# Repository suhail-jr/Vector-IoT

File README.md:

# Vector-IoT
Vector IoT : World’s smallest and powerful fully opensource  fully-featured ESP32 development board designed to unlock the power of the ESP32’s dual-core 240MHz and internet connectivity, in a package smaller than your thumb!

 ~ Current Status: Prototype boards sponsored by [jlcpcb.com](https://jlcpcb.com) ~
     
     Note: This design was performed in Eagle 9.2.0 , you will need a atleast eagle 9.2.0 or higher version to open and edit these source files. 
           # Chance for bugs : High

# Rendered Footage of the PCB

## Licence
 * Hardware in this repository is licenced under Creative Commons BY-SA

 ## OSHW Certification
 TBD (Will apply when prototypes tested)

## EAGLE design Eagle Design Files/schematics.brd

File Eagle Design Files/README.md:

# Vector-IoT
Vector IoT : World’s smallest and powerful fully opensource  fully-featured ESP32 development board designed to unlock the power of the ESP32’s dual-core 240MHz and internet connectivity, in a package smaller than your thumb! Order your pcb from [jlcpcb.com](https://jlcpcb.com)

 ~ Current Status: Prototype boards sponsored by [jlcpcb.com](https://jlcpcb.com) ~
     
     Note: This design was performed in Eagle 9.2.0 , you will need a atleast eagle 9.2.0 or higher version to open and edit these source files. 
           # Chance for bugs : High

# Rendered Footage of the PCB

## Licence
 * Hardware in this repository is licenced under Creative Commons BY-SA

 ## OSHW Certification
 TBD (Will apply when prototypes tested)

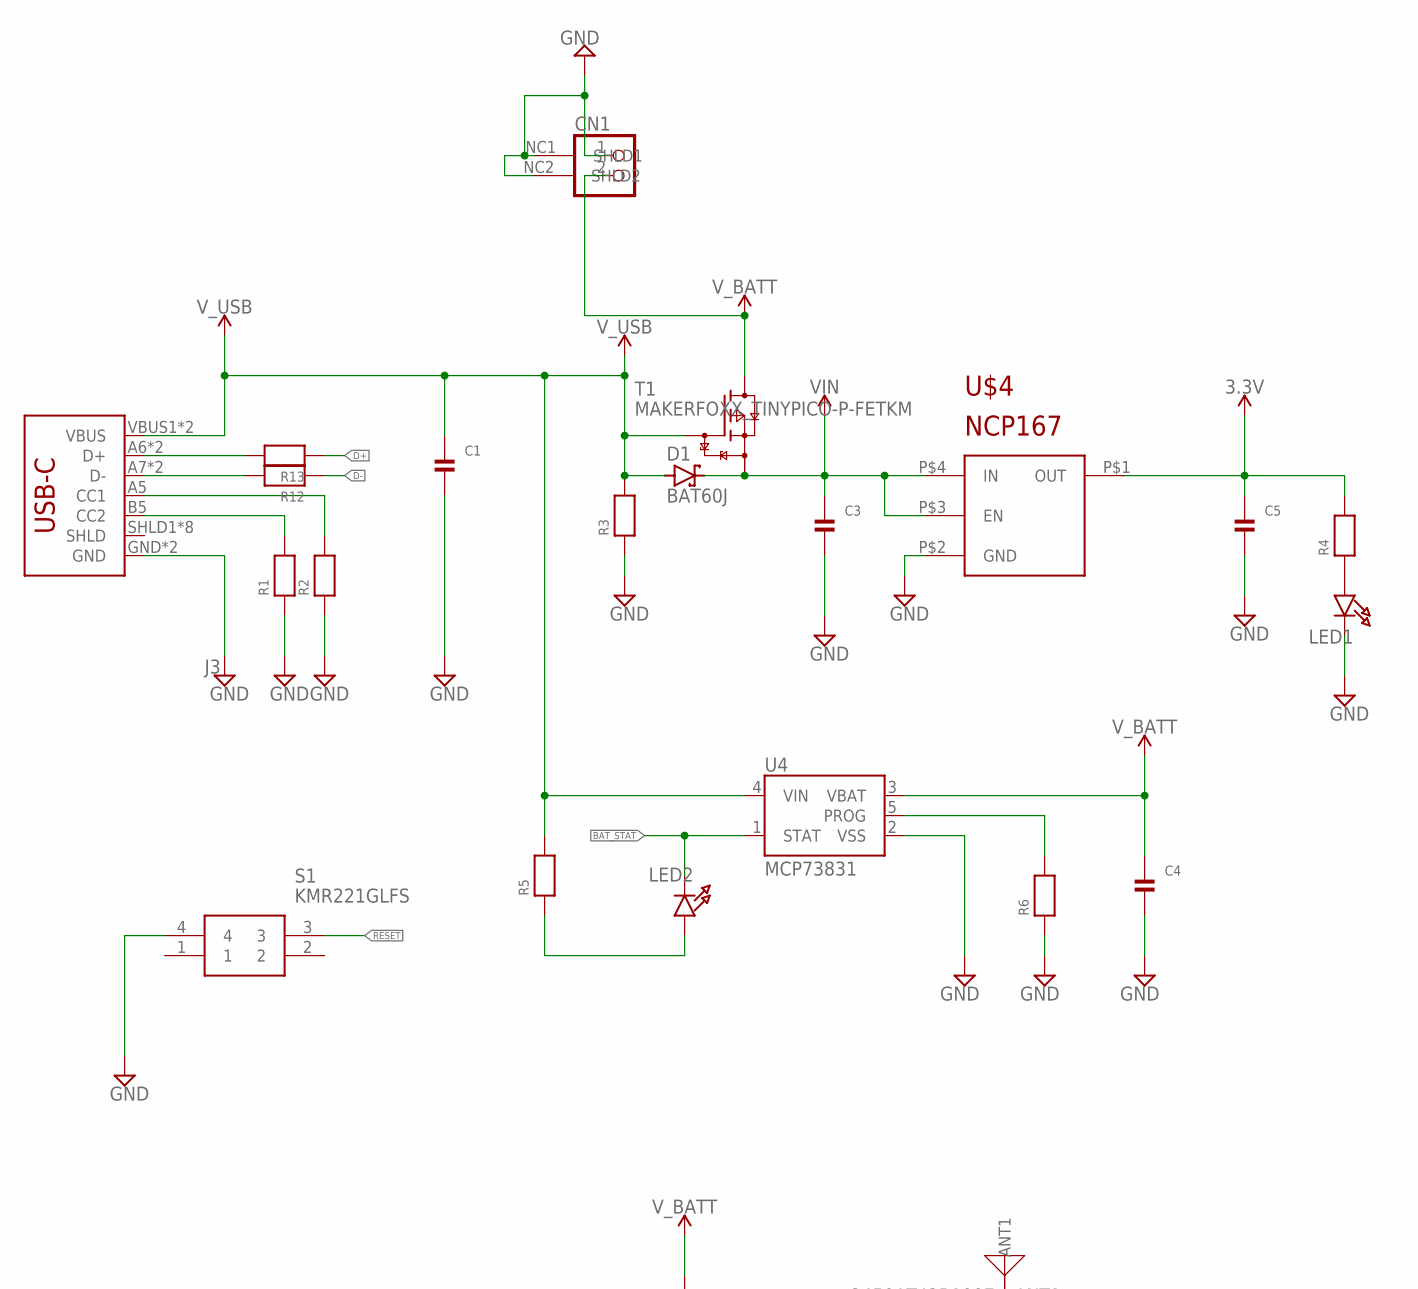
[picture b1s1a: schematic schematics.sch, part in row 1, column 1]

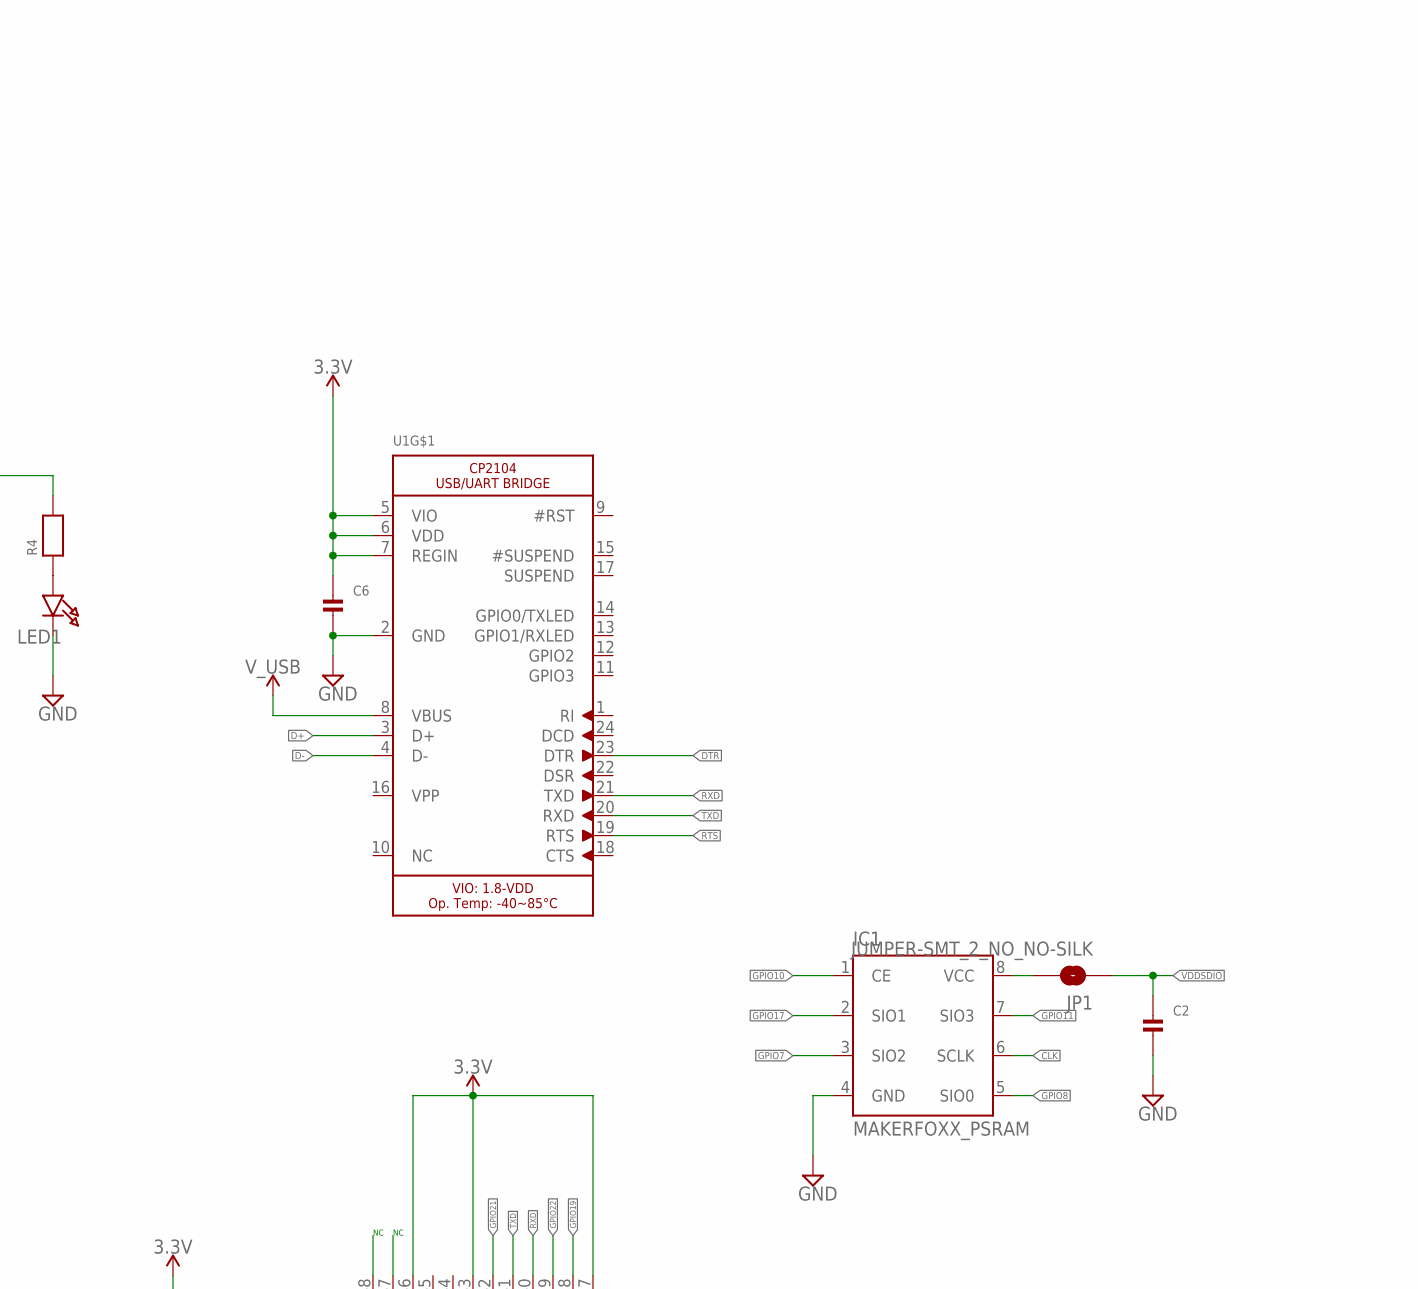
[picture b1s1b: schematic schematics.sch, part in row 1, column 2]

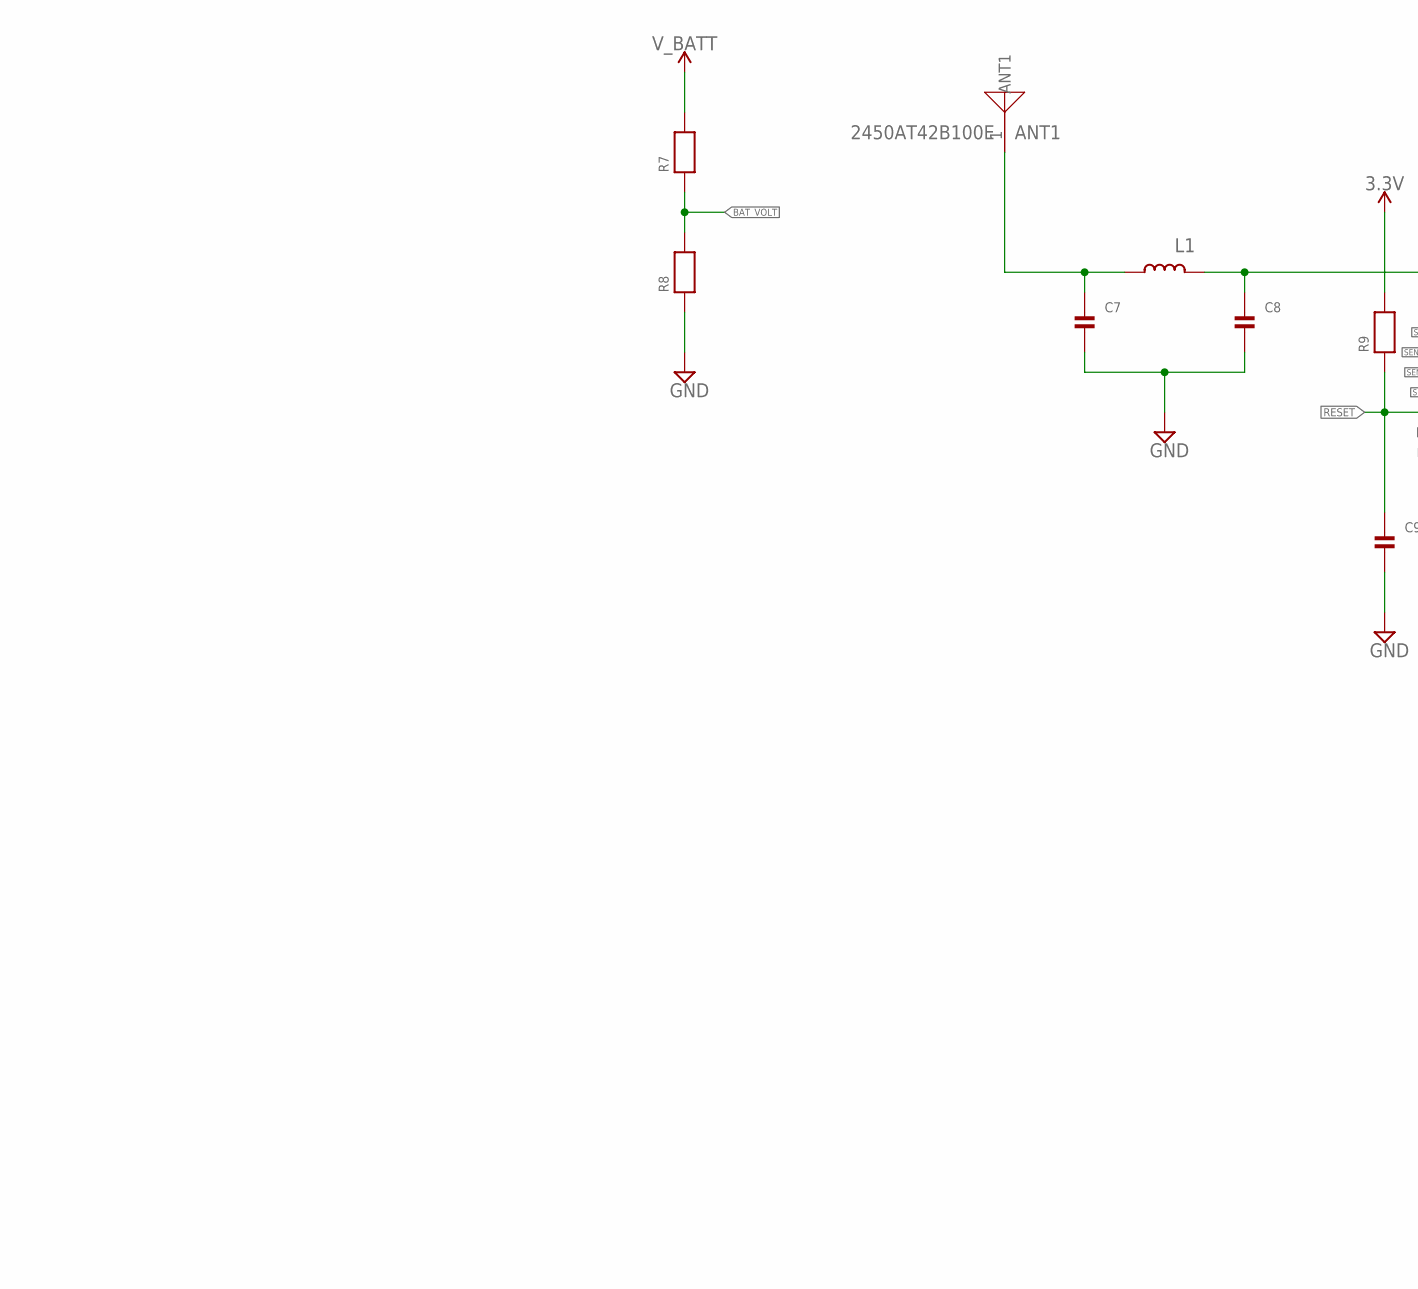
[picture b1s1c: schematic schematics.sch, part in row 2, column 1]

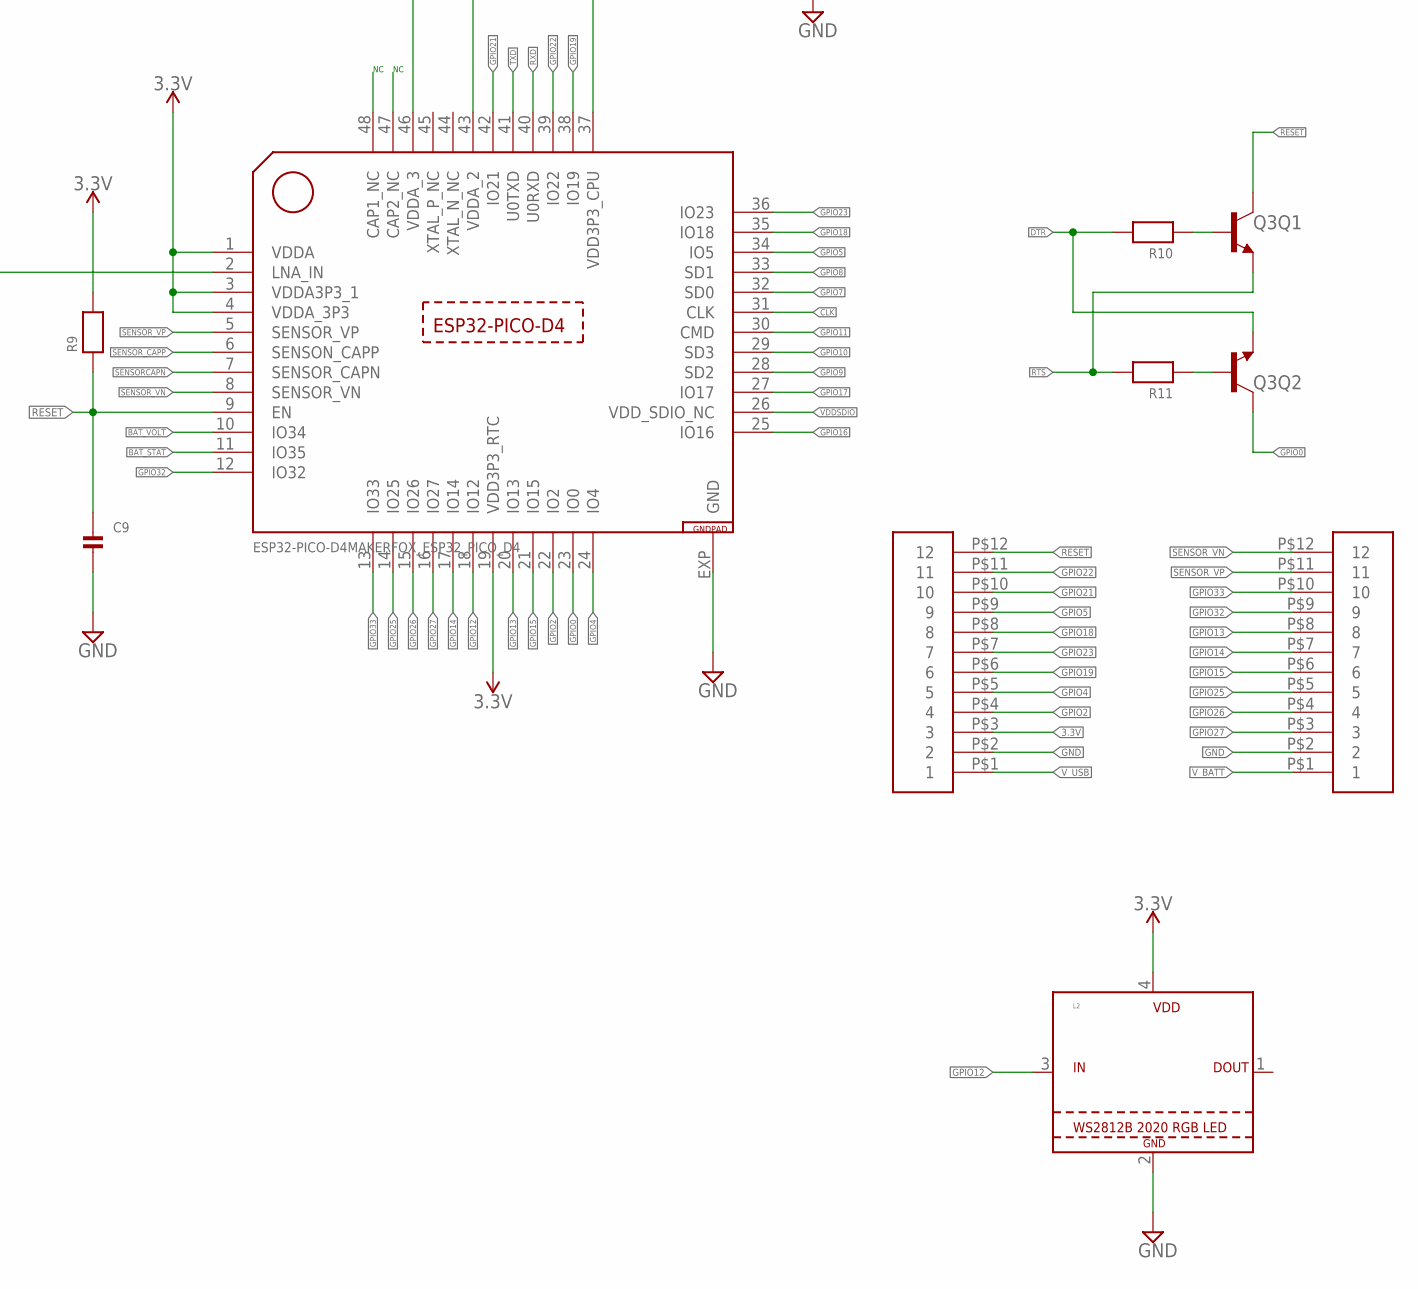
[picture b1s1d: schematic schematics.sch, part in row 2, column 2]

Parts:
ANT1: 2450AT42B100E
C1, C6: CAP_CERAMIC_0603MP; _0603MP
C2, C3, C4, C5, C7, C8, C9: CAP_CERAMIC_0402MP; _0402MP
CN1: STANDARD_JST_2PINSH2; MAKERFOXX_JSTSH2
D1: BAT60J; SOD323_ST
IC1: MAKERFOXX_PSRAM; MAKERFOXX_SOP8
J3: USBC_USB_C5; USBC_USB-C-16P-5
JP1: JUMPER-SMT_2_NO_NO-SILK; SMT-JUMPER_2_NO_NO-SILK
L1: 3.9NH; _0402MP
L2: DISCRETE_NOA_WS2812B2020; DISCRETE_NOA_WS2812_2020
LED1, LED2: LED0603_NOOUTLINE; CHIPLED_0603_NOOUTLINE
Q3: MAKERFOXX_MBT3904DW1T1; MAKERFOXX_DUAL_NPN_SC70-6
R1, R2, R3, R4, R5, R6, R7, R8, R9, R10, R11, R12, R13: RESISTOR_0402MP; _0402MP
S1: KMR221GLFS; KMR2_1
T1: MAKERFOXX_TINYPICO-P-FETKM; MAKERFOXX_SOT883(B)
U1: CP2104_MICROBUILDER_CP2104; CP2104_MICROBUILDER_QFN24_4MM_SMSC
U4: MCP73831; SOT23-5
U$1: ESP32-PICO-D4MAKERFOX_ESP32_PICO_D4; MAKERFOXX_PICO-D4-QFN48
U$2, U$3: MAKEERFOXX_HEADER_12; HEADER_12_NO_SILK
U$4: NCP167; XDFN4

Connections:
3.3V: C5.1, C6.1, L2.4 (VDD), R4.2, R9.2, U1.5 (VIO), U1.6 (VDD), U1.7 (REGIN), U$1.1 (VDDA), U$1.3 (VDDA3P3_1), U$1.4 (VDDA_3P3), U$1.19 (VDD3P3_RTC), U$1.37 (VDD3P3_CPU), U$1.43 (VDDA_2), U$1.46 (VDDA_3), U$3.P$3 (3), U$4.P$1 (OUT)
BAT_STAT: LED2.C, U4.1 (STAT), U$1.11 (IO35)
BAT_VOLT: R7.1, R8.2, U$1.10 (IO34)
CLK: IC1.6 (SCLK), U$1.31 (CLK)
D+: R13.1, U1.3 (D+)
D-: R12.1, U1.4 (D-)
DTR: Q3.1 (E), R10.2, U1.23 (DTR)
GND: C1.2, C2.2, C3.2, C4.2, C5.2, C6.2, C7.2, C8.2, C9.2, CN1.1, CN1.NC1 (SHLD1), CN1.NC2 (SHLD2), IC1.4 (GND), J3.GND, J3.GND2 (GND), L2.2 (GND), LED1.C, R1.1, R2.1, R3.1, R6.1, R8.1, S1.4, U1.2 (GND), U4.2 (VSS), U$1.EXP (GND), U$2.P$2 (2), U$3.P$2 (2), U$4.P$2 (GND)
GPIO0: Q3.6 (C), U$1.23 (IO0)
GPIO2: U$1.22 (IO2), U$3.P$4 (4)
GPIO4: U$1.24 (IO4), U$3.P$5 (5)
GPIO5: U$1.34 (IO5), U$3.P$9 (9)
GPIO7: IC1.3 (SIO2), U$1.32 (SD0)
GPIO8: IC1.5 (SIO0), U$1.33 (SD1)
GPIO9: U$1.28 (SD2)
GPIO10: IC1.1 (CE), U$1.29 (SD3)
GPIO11: IC1.7 (SIO3), U$1.30 (CMD)
GPIO12: L2.3 (DIN), U$1.18 (IO12)
GPIO13: U$1.20 (IO13), U$2.P$8 (8)
GPIO14: U$1.17 (IO14), U$2.P$7 (7)
GPIO15: U$1.21 (IO15), U$2.P$6 (6)
GPIO16: U$1.25 (IO16)
GPIO17: IC1.2 (SIO1), U$1.27 (IO17)
GPIO18: U$1.35 (IO18), U$3.P$8 (8)
GPIO19: U$1.38 (IO19), U$3.P$6 (6)
GPIO21: U$1.42 (IO21), U$3.P$10 (10)
GPIO22: U$1.39 (IO22), U$3.P$11 (11)
GPIO23: U$1.36 (IO23), U$3.P$7 (7)
GPIO25: U$1.14 (IO25), U$2.P$5 (5)
GPIO26: U$1.15 (IO26), U$2.P$4 (4)
GPIO27: U$1.16 (IO27), U$2.P$3 (3)
GPIO32: U$1.12 (IO32), U$2.P$9 (9)
GPIO33: U$1.13 (IO33), U$2.P$10 (10)
IN: C3.1, D1.C, T1.2 (S), U$4.P$3 (EN), U$4.P$4 (IN)
unnamed: LED2.A, R5.1
unnamed: IC1.8 (VCC), JP1.2
unnamed: Q3.5 (B), R10.1
unnamed: R6.2, U4.5 (PROG)
unnamed: LED1.A, R4.1
unnamed: Q3.2 (B), R11.1
unnamed: C8.1, L1.2, U$1.2 (LNA_IN)
unnamed: ANT1.1, C7.1, L1.1
unnamed: J3.A7 (D-), J3.B7 (D-), R12.2
unnamed: J3.A6 (D+), J3.B6 (D+), R13.2
unnamed: J3.A5 (CC1), R2.2
unnamed: J3.B5 (CC2), R1.2
RESET: C9.1, Q3.3 (C), R9.1, S1.3, U$1.9 (EN), U$3.P$12 (12)
RTS: Q3.4 (E), R11.2, U1.19 (RTS)
RXD: U1.21 (TXD), U$1.40 (U0RXD)
SENSORCAPN: U$1.7 (SENSOR_CAPN)
SENSOR_CAPP: U$1.6 (SENSON_CAPP)
SENSOR_VN: U$1.8 (SENSOR_VN), U$2.P$12 (12)
SENSOR_VP: U$1.5 (SENSOR_VP), U$2.P$11 (11)
TP: U1.THERM (TP)
TXD: U1.20 (RXD), U$1.41 (U0TXD)
VDDSDIO: C2.1, JP1.1, U$1.26 (VDD_SDIO_NC)
V_BATT: C4.1, CN1.2, R7.2, T1.3 (D), U4.3 (VBAT), U$2.P$1 (1)
V_USB: C1.1, D1.A, J3.VBUS1 (VBUS), J3.VBUS2 (VBUS), R3.2, R5.2, T1.1 (G), U1.8 (VBUS), U4.4 (VIN), U$3.P$1 (1)

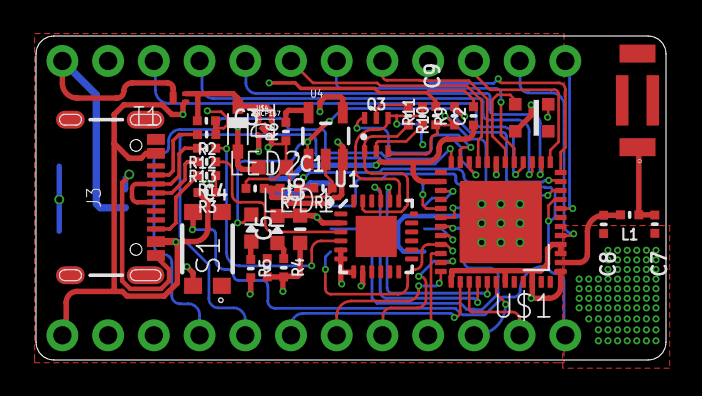
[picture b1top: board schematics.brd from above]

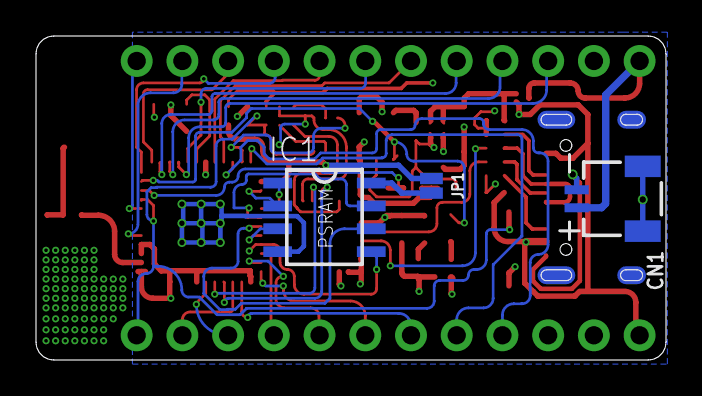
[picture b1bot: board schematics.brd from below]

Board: 4 copper layers, 35.0 x 18.0 mm, 41 parts (3 on the bottom side), 53 nets.

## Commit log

2020-09-05 Added Initial Files
2020-12-29 Changed Directory
2020-12-29 Readme.md
2020-12-29 changed image direcotry

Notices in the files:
parts and their libraries:
SparkFun-IC-Power: Licensing: Creative Commons ShareAlike 4.0 International - https://creativecommons.org/licenses/by-sa/4.0
Microbuilder: This work is placed in the public domain, and may be freely used for commercial and non-commercial work with the following conditions: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
